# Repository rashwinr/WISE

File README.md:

# Wearable Inertial Sensors for Exergames

We are creating a wearable IMUs for ROM (range of motion) assessment and arm rehabilitation of stroke patients.

Data: The data folder consists of data sets saved from the IMU.
Arduino: All scripts relevant to the jacket are placed here.
3D model: All the IMU enclosure for the jacket are placed in this folder.

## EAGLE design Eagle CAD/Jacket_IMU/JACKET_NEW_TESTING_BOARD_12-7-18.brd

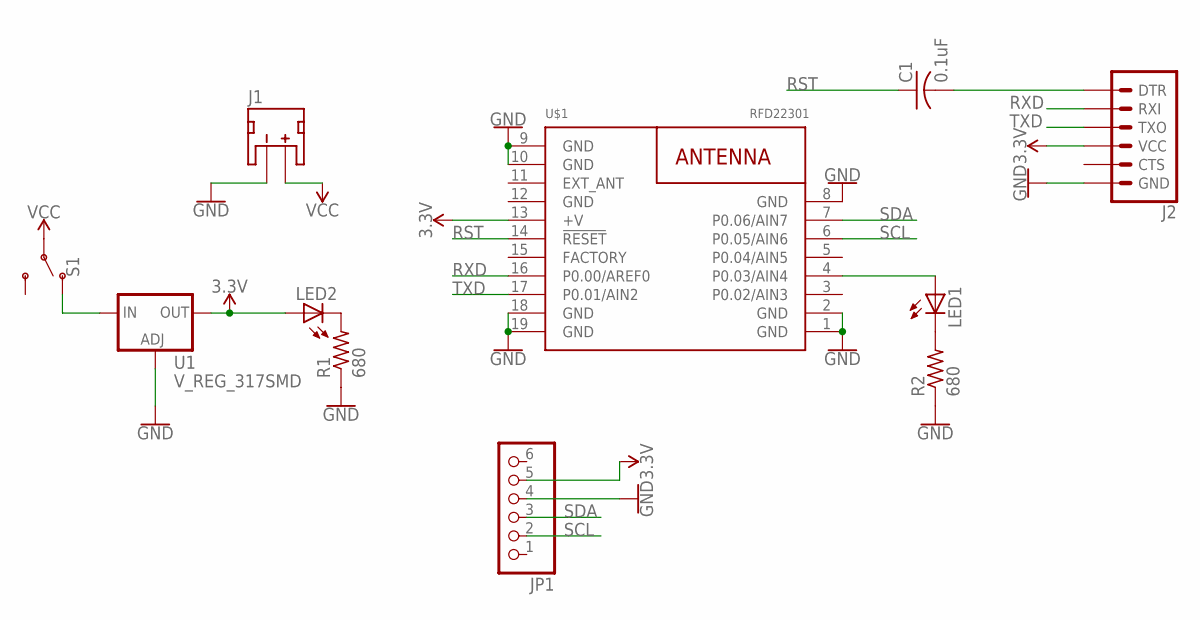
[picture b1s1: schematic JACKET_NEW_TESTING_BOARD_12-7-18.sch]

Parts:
C1: 0.1uF; C0805
J1: JST_2MM_MALE; JST-2-SMD
J2: 6_PIN_SERIAL_TARGET; 1X06
JP1: PINHD-1X6CB; 1X06-CLEANBIG
LED1, LED2: LEDCHIP-LED0805; CHIP-LED0805
R1, R2: 680; R0805
S1: SWITCH-SPDT-PTH-11.6X4.0MM; SWITCH_SPDT_PTH_11.6X4.0MM
U1: V_REG_317SMD; SOT223
U$1: RFD22301

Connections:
3.3V: J2.4 (VCC), JP1.5, LED2.A, U1.2 (OUT), U$1.13 (+V)
GND: J1.1 (-), J2.6 (GND), JP1.4, R1.1, R2.1, U1.1 (ADJ), U$1.1 (GND), U$1.2 (GND), U$1.8 (GND), U$1.9 (GND), U$1.10 (GND), U$1.12 (GND), U$1.18 (GND), U$1.19 (GND)
unnamed: S1.1 (O), U1.3 (IN)
unnamed: LED2.C, R1.2
unnamed: LED1.C, R2.2
unnamed: LED1.A, U$1.4 (P0.03/AIN4)
unnamed: C1.2, J2.1 (DTR)
RST: C1.1, U$1.14 (!RESET!)
RXD: J2.2 (RXI), U$1.16 (P0.00/AREF0)
SCL: JP1.2, U$1.6 (P0.05/AIN6)
SDA: JP1.3, U$1.7 (P0.06/AIN7)
TXD: J2.3 (TXO), U$1.17 (P0.01/AIN2)
VCC: J1.2 (+), S1.2

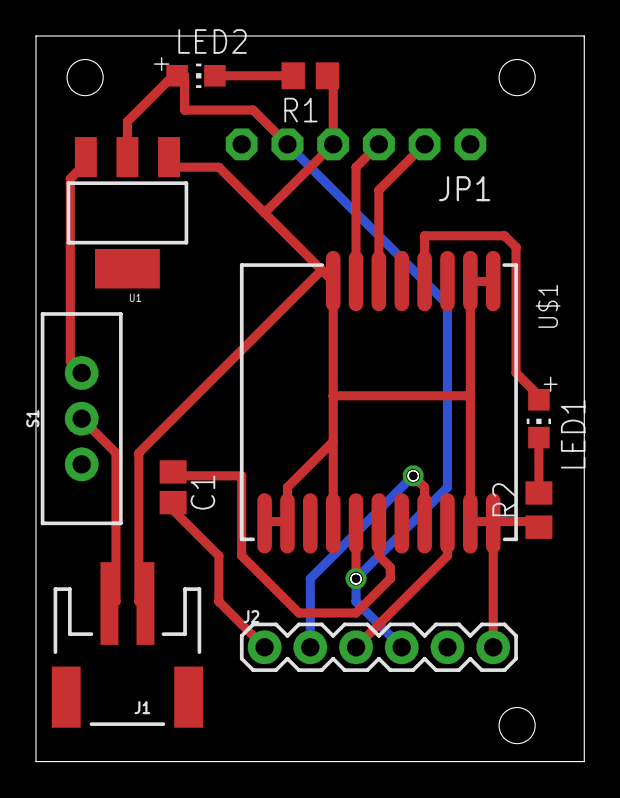
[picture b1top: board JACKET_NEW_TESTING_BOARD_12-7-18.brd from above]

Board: 2 copper layers, 30.5 x 40.3 mm, 11 parts (0 on the bottom side), 13 nets.

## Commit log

2019-02-20 New folders with data, 3D Model, and Arduino scripts have been added
2019-02-20 Added data,3D model, and arduino scripts
2019-02-21 protocol for IMU testing added
2019-02-21 Updated data file with X axis plots
2019-02-21 Added EAGLE CAD Drawings
2019-02-21 Added a .md file of the IMU protocol
2019-02-25 new file arduino i2c comunication without library
2019-02-25 matlab codes for i2c communication with BNO055 single and multiple
2019-02-26 Completed the IMU code with absolute orientation compatible with RFduino
2019-02-28 Master code for RFduino created
2019-03-01 Intermediate changes for reading asbolute angles
2019-03-13 relative orientation plots and codes
2019-03-16 Final version of the RFduino script with IMU
2019-03-27 Kinect supplementary files for matlab with Kinect joint angle assessment script
2019-03-28 Added Unity Code
2019-04-02 Added new 3D model with switch opening, lighting opening
2019-04-02 .STL files added
2019-04-05 Changed dimension based on looking at the actual 3D print
2019-04-08 Playback Added
2019-04-10 <ac_tpose has the transformation necessary to transform imu a as back imu >
2019-04-10 Kinect+IMU's combined partially working, created a new data saving directory
2019-04-12 Added Calibration UI and Unity Scene
2019-04-14 Kinect + IMU & Quaternion codes updated
2019-04-25 calibration box
2019-04-25 calibration box stl
2019-04-26 Added entire unity assets
2019-04-28 Modified version of Kinect with IMU
2019-05-13 <fix functions>
2019-05-26 Updated kinect and IMU code
2019-05-27 fabio_spherical_coordinates_try
2019-05-30 new design
2019-05-31 assemblies new
2019-06-03 Revised Kinect+IMU integration code
2019-06-03 revised codes
2019-06-04 Kin2 modified for face box creation
2019-06-04 Removed unwanted data files
2019-06-04 Kinect code updated with sign and NA text
2019-06-04 changed folder
2019-06-05 Plotting finalized + Fabio LH RH IE
2019-06-06 Added time and multiple animated plots
2019-06-11 new design final
2019-06-12 kinect new code
2019-06-13 newnewdesign
2019-06-13 Parfor implementation and single code for all angle
2019-06-13 Unity Code Updated with Dynamic PlayBack
2019-06-14 Completed version of the code for Kinect IMU comparison
2019-06-14 Replaced files
2019-06-14 Satish commit 5c3e17b pasted with 28b8cfa
2019-06-17 stl model
2019-06-20 New IMU boxes and codes fixed
2019-06-20 Changes in final code
2019-06-20 Updated Unity Assets with new recording UI and Code
2019-06-20 new matlab folder
2019-06-21 New updates
2019-06-21 try functions
2019-06-21 match coordinate frames
2019-06-21 Modified version of the scripts for the new 3D model
2019-06-21 Uploaded New Unity System
2019-06-21 Added entire unity project
2019-06-21 Corrected Left Forearm and added new functoins for refresh
2019-06-24 Completed codes for WISE and kinect comparison
2019-06-24 New final version of scripts
2019-06-25 offsets modification
2019-06-25 static offset and mounting fixing
2019-06-25 Unity Bug Fixes
2019-06-26 Folder organization of all old codes + new peak identification+ modified par for for 10 data points
2019-06-27 Fabios new function to get rid of fscanf
2019-06-28 gaussian distributuons
2019-06-29 Data analysis_whole
2019-06-30 Superdatanalysis code visual
2019-07-01 single patient toroid function plot
2019-07-08 new algorithm for internal external rotation
2019-07-08 fixed new algorithm
2019-07-08 IEEE
2019-07-09 IEEE_spmb details added
2019-07-09 Data for A sensor
2019-07-09 Data for B,C,D sensor
2019-07-10 Data analysis for IEEE SPMB & modified matchframe
2019-07-10 kinect ie algorthm for imu
2019-07-10 New code for all WISE sensors measurement in turntable
2019-07-10 small modifications to IEEE_SPMB data acquisition cumulative
2019-07-10 reduced version of the routine
2019-07-10 IEEE spmb matched data + analysis codes
2019-07-11 new changes to folders
2019-07-12 Image drawing + data + other codes IEEE ISMB
2019-07-13 clock plot with legend
2019-07-14 edited match frame function
2019-07-16 box transformation
2019-07-20 Randon
2019-07-20 New Data analysis folder created
2019-07-20 box_tranf final version
2019-07-22 Final Wise Kinect testing
2019-07-22 Removed Unity Code, Check the New Repository for the Updated Unity Code
2019-07-23 Data of 10 subjects
2019-07-23 JCS folder
2019-07-27 New modified individual wise kinect testing
2019-07-27 Folders rearranged, removed unwanted data
2019-07-27 nothing
2019-07-27 change get left and right for imu int ext sho rot
2019-07-28 Modified kinect for IE
2019-07-28 JCS algorithm for kin+wise
2019-07-28 Minor changes
2019-07-28 new functions and fix in routine
2019-07-29 fixed stuff
2019-07-29 WISE design
2019-07-30 New codes for IEEE sensors
2019-07-31 IEEE Sensors
2019-07-31 new JCS_isb algorithm for KNI+WISE
2019-07-31 animated line of mounting offset and internal external
2019-07-31 New changes
2019-07-31 added text
2019-08-01 Plotting of JCS
2019-08-02 Data analysis updates
2019-08-03 Data analyzed files uploaded
2019-08-03 Data analysis excel sheet updated
2019-08-07 new numbers in IEEE_sensor box_transf
2019-08-07 codes for testing IEEE sensors
2019-08-07 fixed procedure
2019-08-10 Data for IEEE sensors paper processed
2019-08-12 New changes to plotting of JCS
2019-08-13 cost function
2019-08-13 JCS data
2019-08-15 New cost system
2019-08-23 Repeatability and accuracy analysis
2019-08-23 Repeatability and accuracy for IEEEsensors
2019-09-01 Updated data collection and results for mHealth
2019-09-08 DTW_normalized
2019-09-24 Bland Altman with Kimber
2019-09-25 Cronbach alpha, Bland-Altman, Data plotting
2019-09-26 Cronbach alpha + Bland-Altman
2019-09-28 Quaternion code
2019-09-28 Quaternion code modified
2019-10-29 Exergame adaptation loop simulation
2019-11-26 Comments plots for IEEE sensors
2019-12-03 IEEE sensors stable plots
2020-01-29 Kinect+WS4Lymphedema
2020-02-05 For IEEE-BioRob
2020-02-24 New Folder created and organized
2020-02-25 Test routine for therapeutics
2020-03-17 Simple modifications

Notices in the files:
parts and their libraries:
SparkFun-Connectors: Licensing: Creative Commons ShareAlike 4.0 International - https://creativecommons.org/licenses/by-sa/4.0
RFDigital: © 2013 RF Digital Corporation
